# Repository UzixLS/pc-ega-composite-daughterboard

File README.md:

## EGA composite daughterboard
Daughterboard for EGA feature connector, providing CVBS composite video encoder. With this board you can connect your EGA videocard to TV using two RCA jacks, which is usually unused on most EGA cards. One jack is feed by NTSC encoder, other by PAL.

For proper work you must set card to CGA-compatible mode. If card tries to output EGA-Hi-Res modes, composite output will be unsupported by most monitors.

Please note that CGA composite colors will not display properly.

### Jumper setting
* JP1 is not installed - RGBI color mode
* JP1 installed        - RrGgBb color mode (just for testing)
* JP2 is not installed - separate sync for AD724
* JP2 installed        - composite sync for AD724 (just for testing)

Normally both jumper shouldn't be installed.

### Changelog
* Rev.A - initial release
* Rev.A1 - add option to use ISA clock for NTSC encoder; improve power circuit

### Related projects
- https://github.com/monotech/EGA-Mono-Composite-Coverter
- https://github.com/hkzlab/ISA_EGA_CHIPS

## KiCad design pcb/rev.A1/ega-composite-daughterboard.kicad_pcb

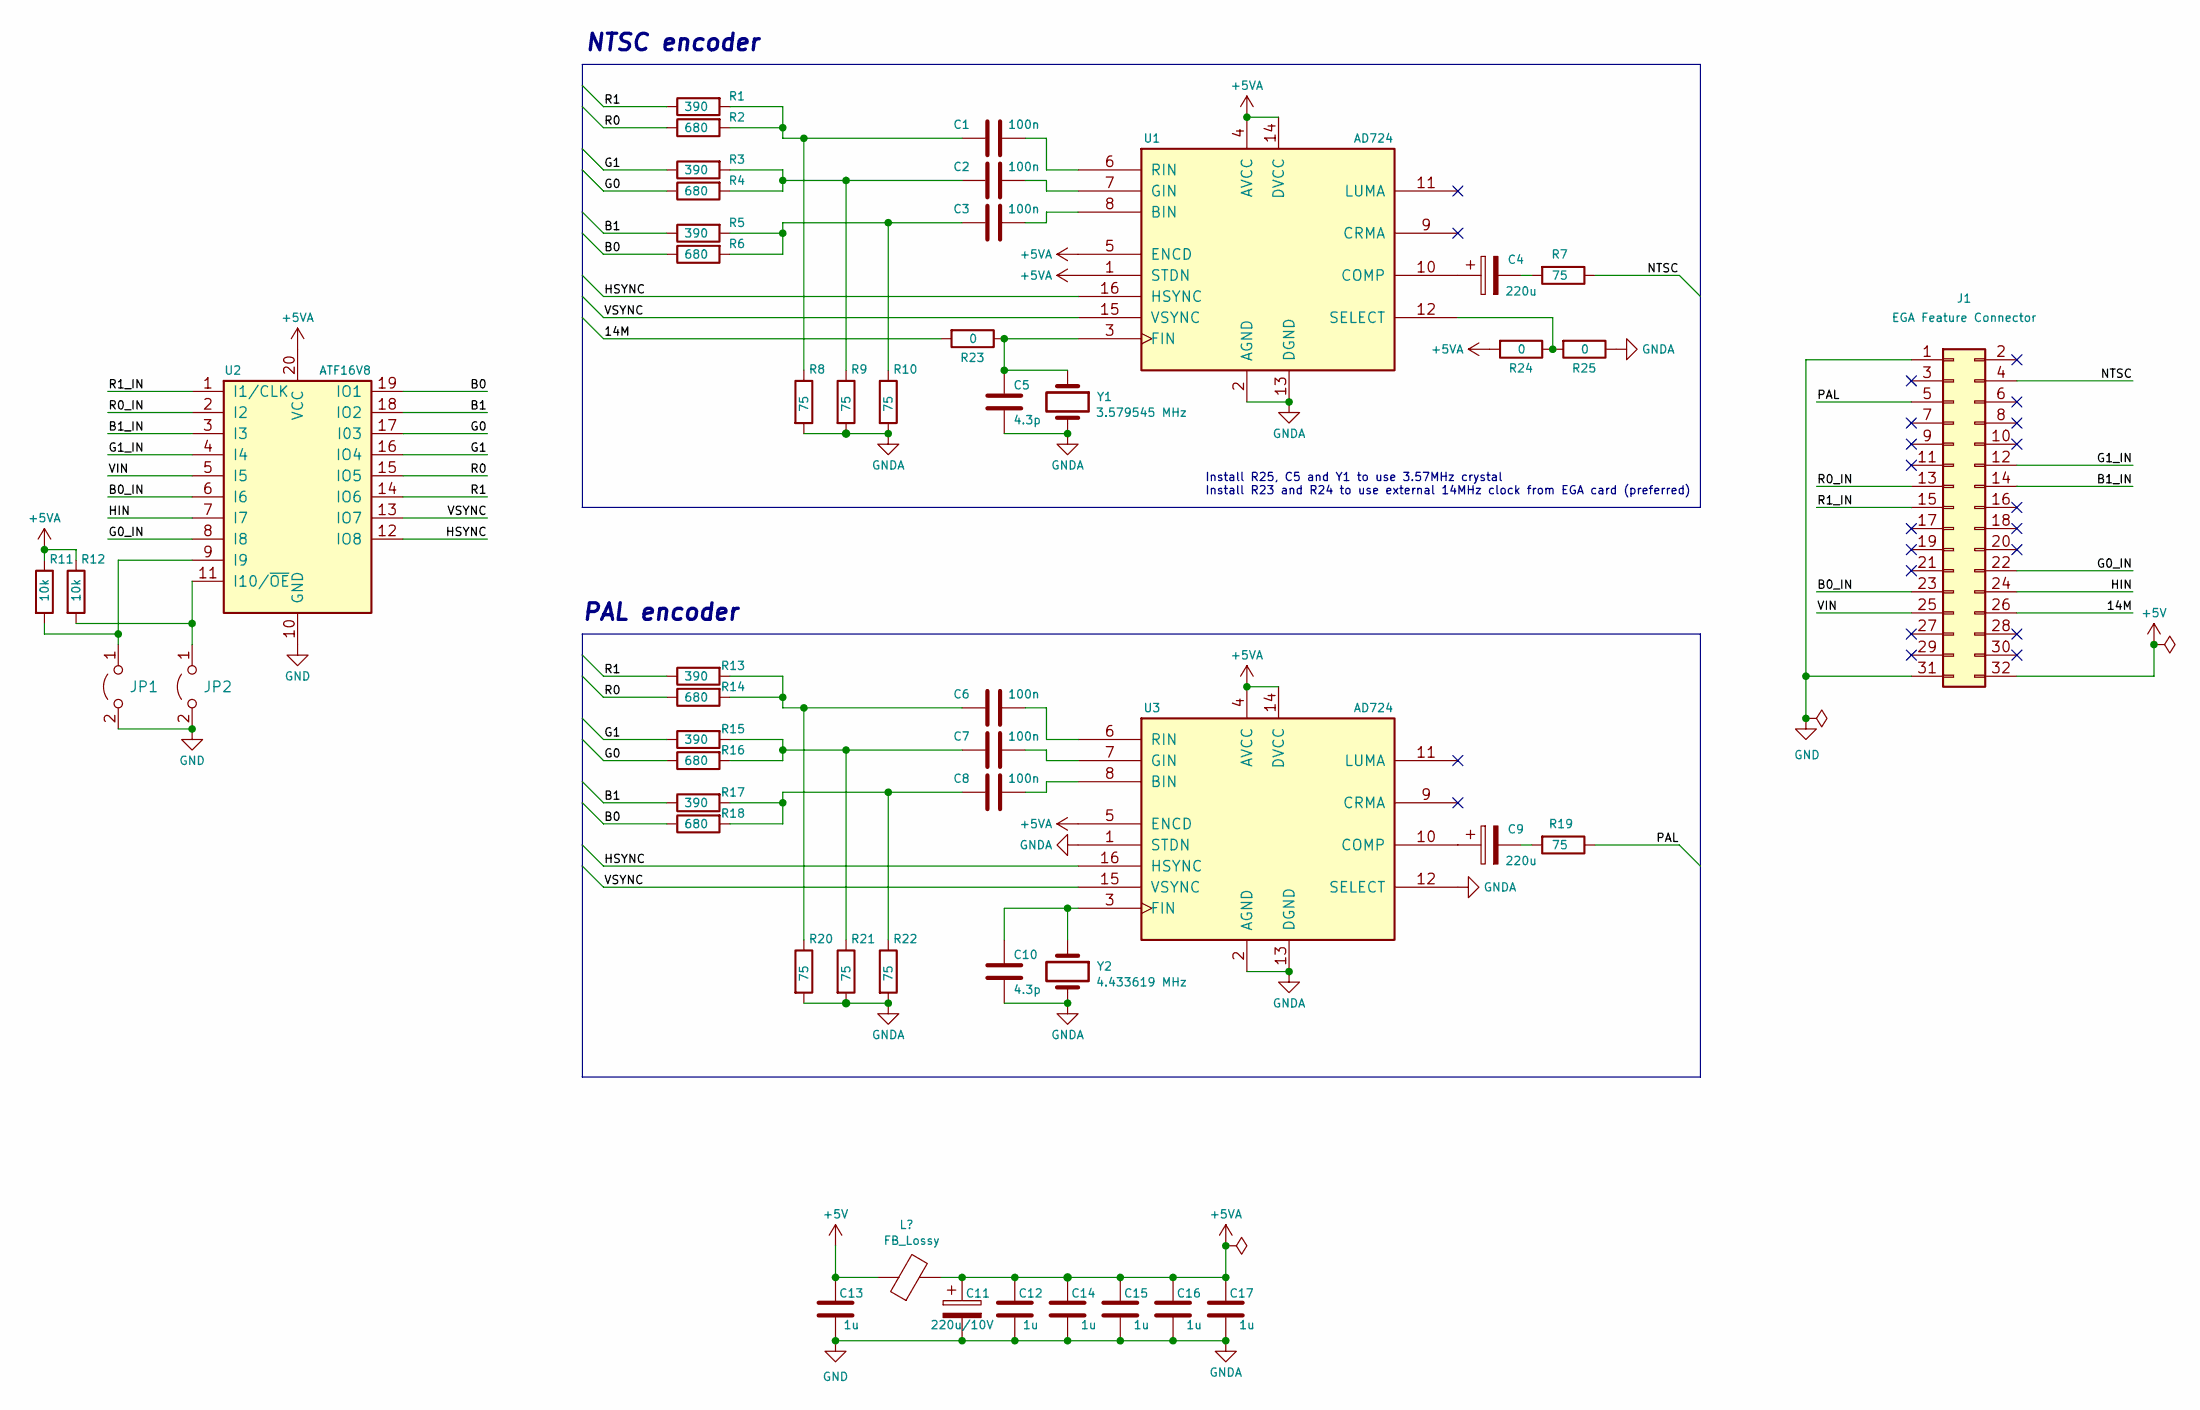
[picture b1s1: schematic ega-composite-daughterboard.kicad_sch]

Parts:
C1, C2, C3, C6, C7, C8: 100n; C_0805_2012Metric_Pad1.18x1.45mm_HandSolder
C4, C9: 220u; CP_Radial_D6.3mm_P2.50mm
C5, C10: 4.3p; C_0805_2012Metric_Pad1.18x1.45mm_HandSolder
C11: 220u/10V; CP_EIA-7343-31_Kemet-D_Pad2.25x2.55mm_HandSolder
C12, C13, C14, C15, C16, C17: 1u; C_0805_2012Metric_Pad1.18x1.45mm_HandSolder
FB1: FB_Lossy; L_Axial_L5.3mm_D2.2mm_P7.62mm_Horizontal_Vishay_IM-1
J1: EGA Feature Connector; PinHeader_2x16_P2.54mm_Vertical
JP1, JP2: Jumper_2_Open; PinHeader_1x02_P2.54mm_Vertical
R1, R3, R5, R13, R15, R17: 390; R_0805_2012Metric_Pad1.20x1.40mm_HandSolder
R2, R4, R6, R14, R16, R18: 680; R_0805_2012Metric_Pad1.20x1.40mm_HandSolder
R7, R8, R9, R10, R19, R20, R21, R22: 75; R_0805_2012Metric_Pad1.20x1.40mm_HandSolder
R11, R12: 10k; R_0805_2012Metric_Pad1.20x1.40mm_HandSolder
R23, R24, R25: 0; R_0805_2012Metric_Pad1.20x1.40mm_HandSolder
U1, U3: AD724; SOIC-16W_7.5x10.3mm_P1.27mm
U2: ATF16V8; DIP-20_W7.62mm
Y1: 3.579545 MHz; Crystal_HC49-4H_Vertical
Y2: 4.433619 MHz; Crystal_HC49-4H_Vertical

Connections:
+5V: C13.2, FB1.1, J1.32
+5VA: C11.1, C12.2, C14.2, C15.2, C16.2, C17.2, FB1.2, R11.1, R12.1, R24.2, U1.1 (STDN), U1.4 (AVCC), U1.5 (ENCD), U1.14 (DVCC), U2.20 (VCC), U3.4 (AVCC), U3.5 (ENCD), U3.14 (DVCC)
/14M: J1.26, R23.2
/B0: R6.1, R18.1, U2.19 (IO1)
/B0_IN: J1.23, U2.6 (I6)
/B1: R5.1, R17.1, U2.18 (IO2)
/B1_IN: J1.14, U2.3 (I3)
/G0: R4.1, R16.1, U2.17 (I03)
/G0_IN: J1.22, U2.8 (I8)
/G1: R3.1, R15.1, U2.16 (IO4)
/G1_IN: J1.12, U2.4 (I4)
/HIN: J1.24, U2.7 (I7)
/HSYNC: U1.16 (HSYNC), U2.12 (IO8), U3.16 (HSYNC)
/NTSC: J1.4, R7.1
/PAL: J1.5, R19.1
/R0: R2.1, R14.1, U2.15 (IO5)
/R0_IN: J1.13, U2.2 (I2)
/R1: R1.1, R13.1, U2.14 (IO6)
/R1_IN: J1.15, U2.1 (I1/CLK)
/VIN: J1.25, U2.5 (I5)
/VSYNC: U1.15 (VSYNC), U2.13 (IO7), U3.15 (VSYNC)
GND: C5.2, C10.2, C11.2, C12.1, C13.1, C14.1, C15.1, C16.1, C17.1, J1.1, J1.31, JP1.2 (B), JP2.2 (B), R8.2, R9.2, R10.2, R20.2, R21.2, R22.2, R25.1, U1.2 (AGND), U1.13 (DGND), U2.10 (GND), U3.1 (STDN), U3.2 (AGND), U3.12 (SELECT), U3.13 (DGND), Y1.2, Y2.2
unnamed: C1.2, R1.2, R2.2, R8.1
unnamed: C2.2, R3.2, R4.2, R9.1
unnamed: C3.2, R5.2, R6.2, R10.1
unnamed: C4.2, R7.2
unnamed: C6.2, R13.2, R14.2, R20.1
unnamed: C7.2, R15.2, R16.2, R21.1
unnamed: C8.2, R17.2, R18.2, R22.1
unnamed: C9.2, R19.2
unnamed: JP1.1 (A), R11.2, U2.9 (I9)
unnamed: JP2.1 (A), R12.2, U2.11 (I10/~OE)
unnamed: C3.1, U1.8 (BIN)
unnamed: C4.1, U1.10 (COMP)
unnamed: C5.1, R23.1, U1.3 (FIN), Y1.1
unnamed: C2.1, U1.7 (GIN)
unnamed: C1.1, U1.6 (RIN)
unnamed: R24.1, R25.2, U1.12 (SELECT)
unnamed: C8.1, U3.8 (BIN)
unnamed: C9.1, U3.10 (COMP)
unnamed: C10.1, U3.3 (FIN), Y2.1
unnamed: C7.1, U3.7 (GIN)
unnamed: C6.1, U3.6 (RIN)

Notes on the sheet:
PAL encoder
NTSC encoder
Install R25, C5 and Y1 to use 3.57MHz crystal Install R23 and R24 to use external 14MHz clock from EGA card (preferred)

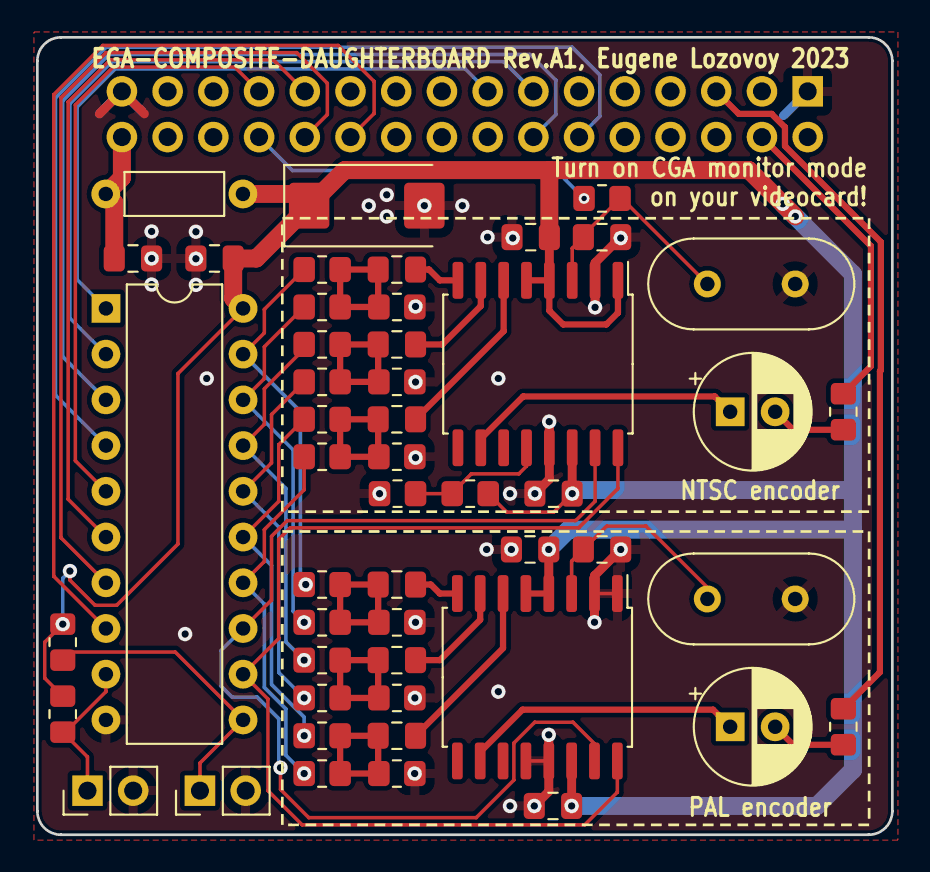
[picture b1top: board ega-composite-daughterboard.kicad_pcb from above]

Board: 2 copper layers, 47.5 x 44.3 mm, 51 parts (1 on the bottom side), 43 nets.

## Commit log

2023-06-21 initial
2023-06-21 wip pcb rev.A
2023-10-01 update gitignore
2023-10-16 add atf/gal firmware
2023-10-16 rename project files
2023-10-16 add pcb rev.A1 files
2023-10-16 add license
